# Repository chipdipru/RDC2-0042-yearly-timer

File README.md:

# RDC2-0042-yearly-timer
Таймер позволяет управлять реле по расписанию в любой день на протяжении года. Расписание составляется в удобной форме в программе на ПК, и записывается в память таймера через порт USB. Реальное время таймера синхронизируется в системным временем персонального компьютера. В устройство встроена резервная батарея бесперебойного хода часов в течение года. 
Примеры использования:
Управление электрическим обогревателем или теплыми полами. Обогреватель будет включаться в заданное время. Например - включение за час до прихода владельца и выключение поздно вечером, затем включение за полчаса до пробуждения и выключение в момент ухода на работу.
Автополив растений. Для регулярного увлажнения грунта на участке во время отпуска или командировки.
Аквариум: управление светом и подачей воздуха в аквариумах 
Имитация присутствия: при долгом отсутствии хозяев дома таймер может имитировать эффект присутствия (к нескольким запрограммированным таймерам можно подключить разные нагрузки - светильники в комнатах, радиоприемник, телевизор и другие приборы, которые будут автоматически включаться и отключаться в заданное время).
Утреннее включение бытовых приборов: чайники, кофеварки, увлажнители воздуха... Можно использовать прибор в качестве будильника (подключив к таймеру любое электрооборудование: ТВ, магнитолу, радиоприемник, свет).
Освещение на улице или во дворе, по расписанию. С помощью таймера можно организовать использование электроприборов только в ночное время суток. В квартирах с многотарифным учетом электричества, что значительно сократит расходы на электроэнергию.
Освещением рекламных баннеров, щитов, фасадов зданий, уличных витрин магазинов.
Технические характеристики
•	Цикл работы - годовой (366 дней)
•	Шаг установки - 1 мин.
•	Количество событий (on/off) - 1524
•	Время автономной работы часов   - 1 год.
•	Потребляемая мощность - не более 1 Вт
•	Напряжение питания DC – 5В
•	Настройка – USB ПК
•	Синхронизация часов – системное время ПК
•	Формат файла расписания - .txt
•	Размер платы мм – 50,8 x 50,8 x 10,0

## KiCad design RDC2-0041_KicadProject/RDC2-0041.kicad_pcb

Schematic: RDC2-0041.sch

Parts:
C1, C2, C6, C7, C8, C10, C11, C12: 0,1мкФ; C_0603_HandSoldering
C3, C5: 4,7мкФ; C_0603_HandSoldering
C4: 0,01мкФ; C_0603_HandSoldering
C9: 10мкФ; TantalC_SizeA_EIA-3216_HandSoldering_mm
DA1: LP2985AIM5-3.3; SOT-23-5_mm
DD1: DS3231; SOIC-16_7.5x10.3mm_Pitch1.27mm
DD2: STM32F042K6Tx; LQFP-32_7x7mm_Pitch0.8mm
DD3: 25LC_EEPROM; SOIC-8_3.9x4.9mm_Pitch1.27mm
HL1: LTV-817; LTV817S
HL2, HL4, HL5, HL6: 7SEGMENTS; Oasistek_7SegInd_smd
HL3: LED; LED_0603_HandSoldering
R1, R6: 330R; R_0603_HandSoldering
R2, R7, R8, R9, R10, R11, R12, R13, R14, R25: 10k; R_0603_HandSoldering
R3: 0R; R_0603_HandSoldering
R4, R5: 4k7; R_0603_HandSoldering
R15, R16, R17, R18, R19, R20, R21, R22: 300; R_0603_HandSoldering
R23, R24: 22R; R_0603_HandSoldering
SW1: SW_PUSH; TC-0120
VD1: USBLC6; SOT23-6L
VD2: D; SOD-123
VT1, VT2, VT3, VT4: BSS138; SOT-23_mm
XP1: PLS-2; KLS5-CR1220-01
XP2: CONN_01X03; Clem_3Pos_P5
XP3, XP5, XP6: PLS-2; Pin_Header_Straight_1x02_mm
XP4: CONN_01X03; Pin_Header_Straight_1x03_mm
XP7: CONN_01X04; Pin_Header_Straight_1x04_mm
XP8: CONN_01X04; pin_header-4-1.5_pitch
XS1: USB_OTG; Micro_USB_ElecFreaks

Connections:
5V: C3.1, C11.1, DA1.1 (IN), DA1.3 (EN), VD1.5 (VDD), VD2.1, XP4.3, XP5.1
DIG_1: DD2.14, R11.2, VT4.1
DIG_2: DD2.15, R10.2, VT3.1
DIG_3: DD2.29, R9.2, VT2.1
DIG_4: DD2.30, R8.2, VT1.1
DISPLAY_ON: C12.1, DD2.8, R25.1, SW1.1
GND: C1.2, C2.2, C3.2, C4.2, C5.2, C6.2, C7.2, C8.2, C9.2, C10.2, C11.2, C12.2, DA1.2 (GND), DD1.5, DD1.6, DD1.7, DD1.8, DD1.9, DD1.10, DD1.11, DD1.12, DD1.13, DD2.16, DD2.32, DD3.4, HL3.1 (K), R7.2, R8.1, R9.1, R10.1, R11.1, R13.1, SW1.2, VD1.2 (GND), VT1.2, VT2.2, VT3.2, VT4.2, XP1.2, XP3.1, XP5.2, XP7.3, XP8.4, XS1.5 (GND), XS1.6 (shield)
Gout: HL1.3, XP2.3, XP3.2
LED_1: HL2.7, HL4.7, HL5.7, HL6.7, R21.2
LED_2: HL2.6, HL4.6, HL5.6, HL6.6, R17.2
LED_3: HL2.4, HL4.4, HL5.4, HL6.4, R19.2
LED_4: HL2.2, HL4.2, HL5.2, HL6.2, R15.2
LED_5: HL2.1, HL4.1, HL5.1, HL6.1, R20.2
LED_6: HL2.9, HL4.9, HL5.9, HL6.9, R18.2
LED_7: HL2.10, HL4.10, HL5.10, HL6.10, R22.2
LED_8: HL2.5, HL4.5, HL5.5, HL6.5, R16.2
unnamed: C4.1, DA1.4 (BP)
unnamed: DD1.4, R3.2
unnamed: DD1.14, XP1.1
unnamed: DD1.15, DD2.2, R4.2
unnamed: DD1.16, DD2.3, R5.2
unnamed: DD2.7, R15.1
unnamed: DD2.9, R19.1
unnamed: DD2.10, R16.1
unnamed: DD2.11, R20.1
unnamed: DD2.12, R17.1
unnamed: DD2.13, R21.1
unnamed: DD2.18, R18.1
unnamed: DD2.19, R22.1
unnamed: DD2.21, R23.1
unnamed: DD2.22, R24.1
unnamed: DD2.31, R6.1, R7.1, XP6.1
unnamed: HL1.1, R1.2
unnamed: HL1.4, R2.1, XP2.2
unnamed: HL2.3, HL2.8, VT1.3
unnamed: HL3.2 (A), R6.2
unnamed: HL4.3, HL4.8, VT2.3
unnamed: HL5.3, HL5.8, VT3.3
unnamed: HL6.3, HL6.8, VT4.3
unnamed: VD1.1 (IN1), XP8.2, XS1.2 (D-)
unnamed: VD1.3 (IN2), XP8.3, XS1.3 (D+)
unnamed: VD2.2, XP8.1, XS1.1 (VCC)
RELAY: DD2.20, HL1.2
RST: C2.1, DD2.4, R3.1
RTC_ALARM: DD1.3, DD2.6, R14.1
SPI_MISO: DD2.27, DD3.2
SPI_MOSI: DD2.28, DD3.5
SPI_NSS: DD2.25, DD3.1, R12.1
SPI_SCK: DD2.26, DD3.6, R13.2
SWCLK: DD2.24, XP7.4
SWDIO: DD2.23, XP7.2
USB_DM: R23.2, VD1.6 (OUT1)
USB_DP: R24.2, VD1.4 (OUT2)
VDD: C1.1, C5.1, C6.1, C7.1, C8.1, C9.1, C10.1, DA1.5 (OUT), DD1.2, DD2.1, DD2.5, DD2.17, DD3.3, DD3.7, DD3.8, R1.1, R4.1, R5.1, R12.2, R14.2, R25.2, XP4.1, XP6.2, XP7.1
Vout: R2.2, XP2.1, XP4.2

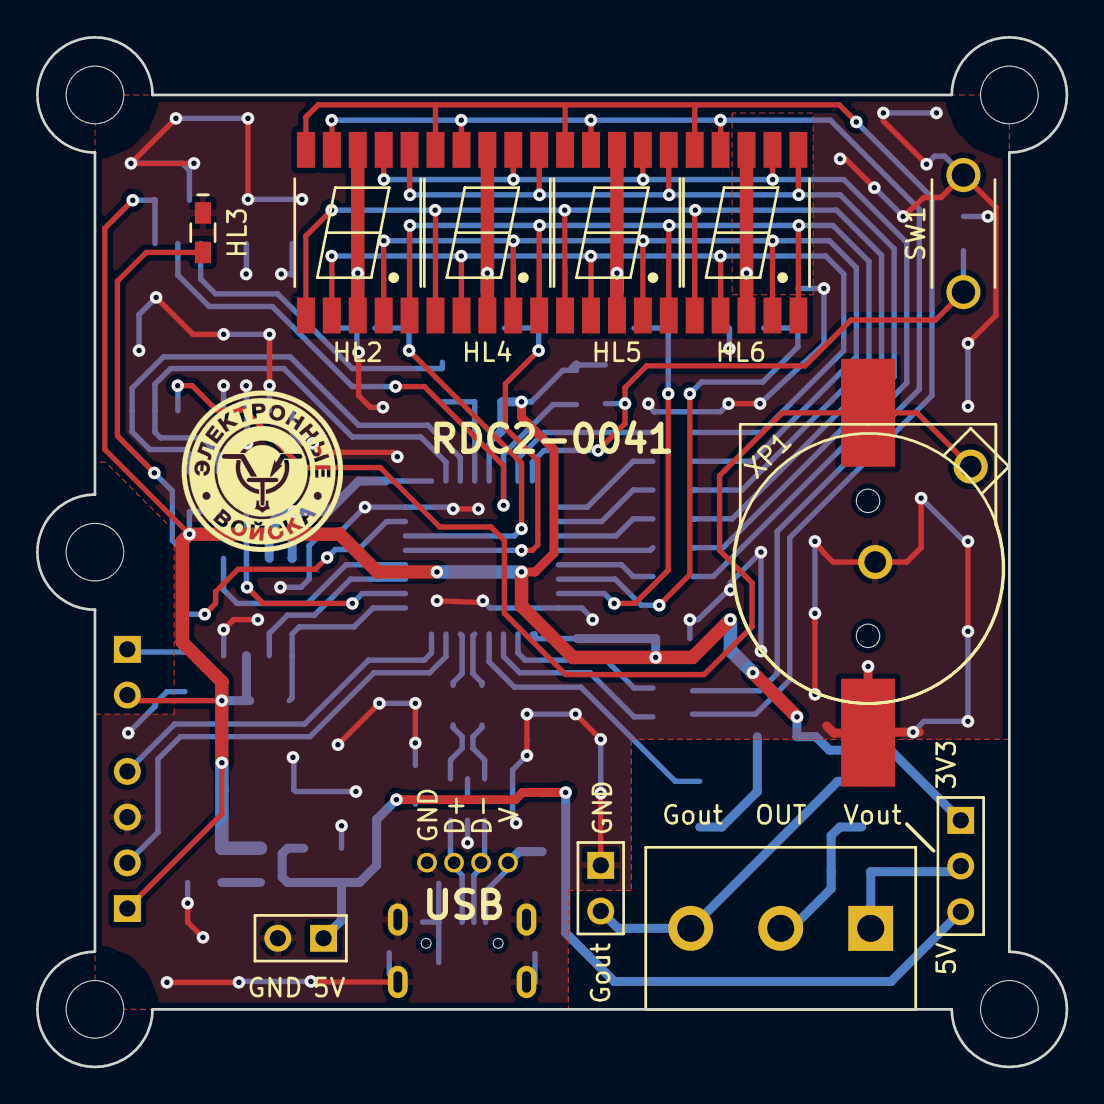
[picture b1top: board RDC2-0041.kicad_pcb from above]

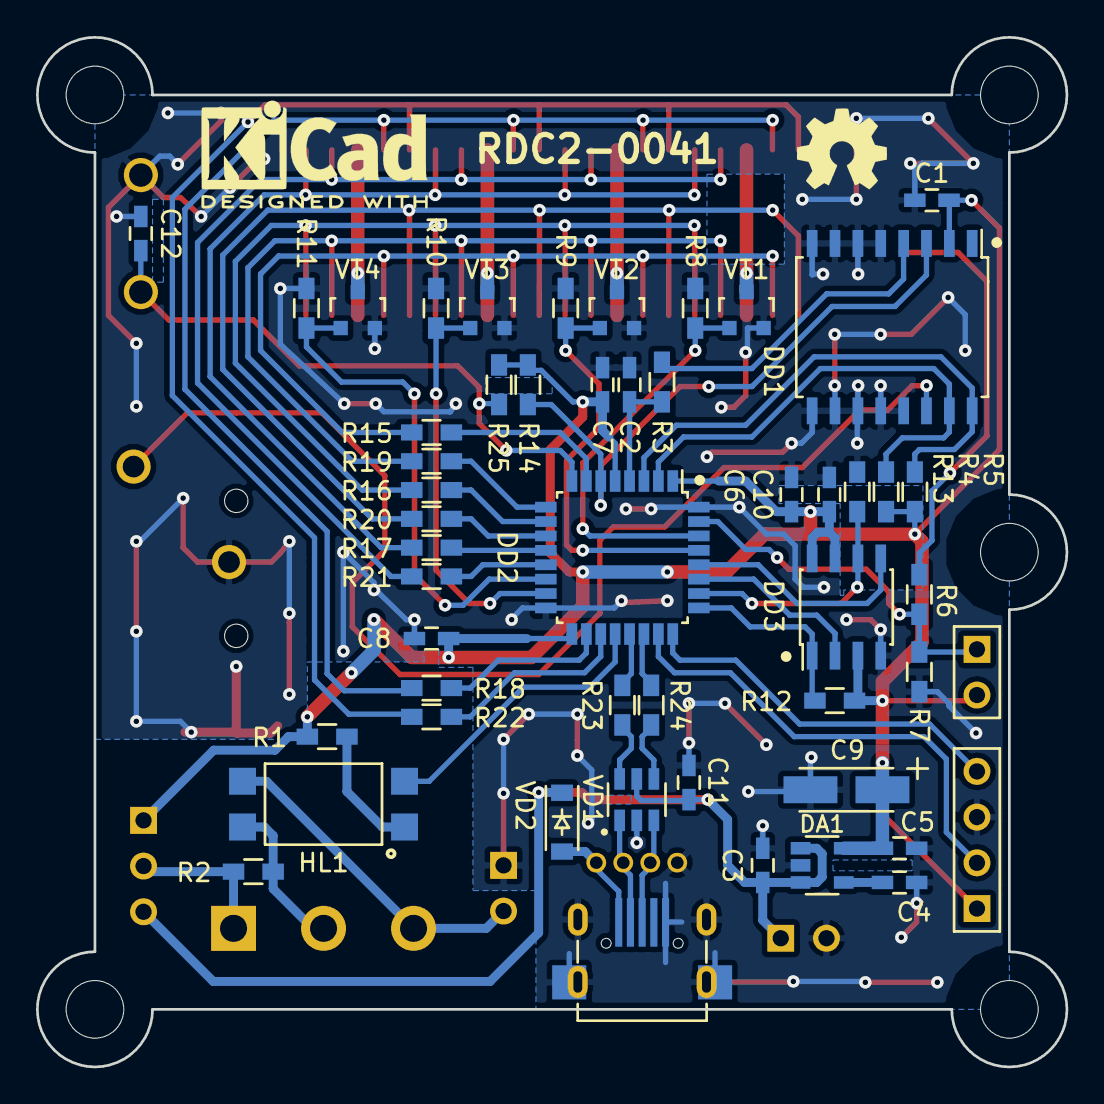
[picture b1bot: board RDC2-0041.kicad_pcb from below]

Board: 2 copper layers, 57.2 x 57.2 mm, 63 parts (52 on the bottom side), 55 nets.

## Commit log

2018-10-02 Прошивка DFU
2018-10-02 soft для настроек
2018-10-02 IAR project
2018-10-02 visual studio project
2018-10-02 KiCad project
2018-10-02 инструкция описание
